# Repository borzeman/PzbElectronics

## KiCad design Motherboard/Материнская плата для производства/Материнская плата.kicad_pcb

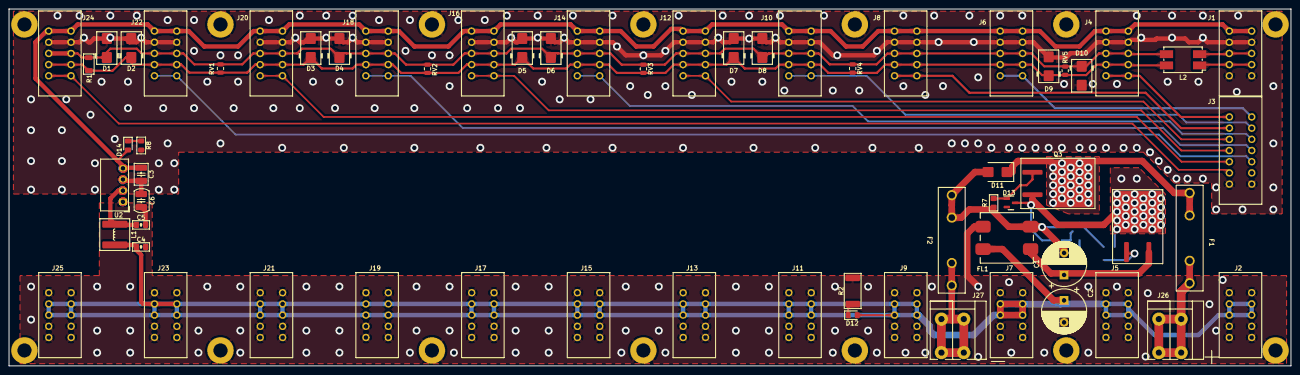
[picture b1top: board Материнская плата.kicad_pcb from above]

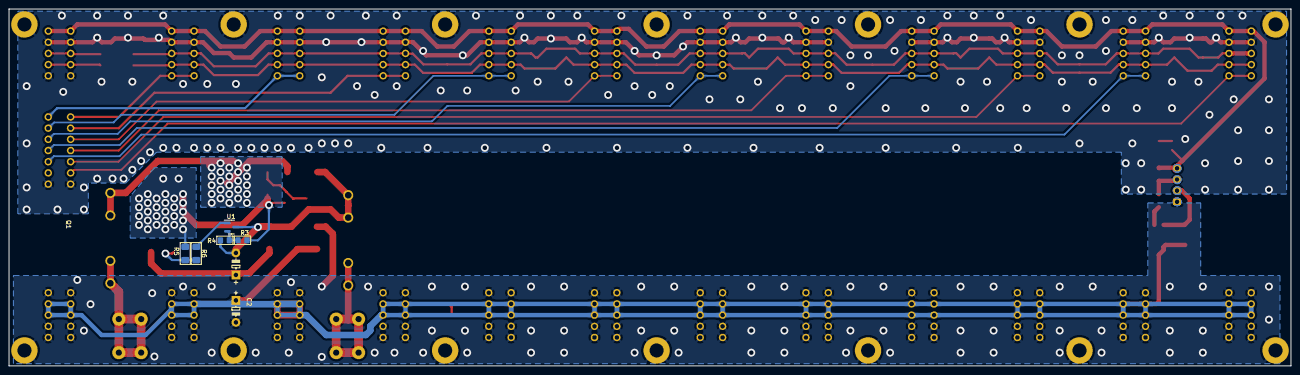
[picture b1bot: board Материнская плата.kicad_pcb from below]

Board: 2 copper layers, 291.0 x 81.0 mm, 83 parts (5 on the bottom side), 32 nets.

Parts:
C1, C2: 47uF 63V D10 H16; CP_Radial_D10.0mm_P5.00mm
C3: 10uF 50V 1210 GRM32ER71H106K; C_1210_3225Metric_Pad1.42x2.65mm_HandSolder
C4, C5: 4,7uF 50V 0805; C_0805_2012Metric_Pad1.18x1.45mm_HandSolder
C6: 270 pf X7R 1206 2000v 202R18W271KW4E; C_1210_3225Metric_Pad1.42x2.65mm
D1, D2, D3, D4, D5, D6, D7, D8, D9, D10: SMBJ5.0A (SMB); D_SMB
D11: SM6T30A (SMB); D_SMB
D12, D14: LED 0805 (FYLS-0805UBC); LED_0805_2012Metric_Pad1.15x1.40mm_HandSolder
D13: BZX84C10 (SOT-23); SOT-23
F1, F2: Fuse 10A ZH266 (2 клипсы); Fuseholder_100_series_5x20mm_D1,5
FL1: ACM70V-701-2PL-TL00; ACM12V
H1, H2, H3, H4, H5, H6, H7, H8, H9, H10, H11, H12, H13, H14: MountingHole_M3_3.2mm_Pad; MountingHole_3.2mm_Pad
J1, J2, J4, J5, J6, J7, J8, J9, J10, J11, J12, J13, J14, J15, J16, J17, J18, J19, J20, J21, J22, J23, J24, J25: SL-10 (L-KLS1-603C-10-S)
J3: SL-14 (L-KLS1-603C-14-S)
J26, J27: DG142V-5.08-02P-14
L1: 6,8uH 3,5A ETQP3M6R8KVP; L_Bourns-SRN6028
L2: B82790S0253N201; L_CommonMode_Delevan_4222
Q1, Q3: SUM110P06-08L-E3 (TO-263-2); TO-263-2
R1: 1206-120 Ом±5%-0,25 Вт; R_1206_3216Metric
R2: 2512-2,4 кОм±5%-1 Вт; R_2512_6332Metric_Pad1.52x3.35mm_HandSolder
R3, R7: 0805-10 кОм±5%-0,125 Вт; R_0805_2012Metric_Pad1.20x1.40mm_HandSolder
R4: 0805-1,5 кОм±5%-0,125 Вт; R_0805_2012Metric_Pad1.20x1.40mm_HandSolder
R5, R6: 1206-1 кОм±5%-0,25 Вт; R_1206_3216Metric_Pad1.42x1.75mm_HandSolder
R8: 0805-200 Ом±5%-0,125 Вт; R_0805_2012Metric_Pad1.15x1.40mm
RV1, RV2, RV3, RV4, RV5: JMV0805S5R6T661; R_0805_2012Metric
U1: TL431DBZ (sot-23); SOT-23
U2: AM1SS-2403SJZ; Converter_DCDC_Murata_CRE1xxxxxx3C_THT

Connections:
+24V: C2.1, C4.1, D12.2 (A), FL1.4, J2.2, J2.3, J2.8, J2.9, J5.2, J5.3, J5.8, J5.9, J7.2, J7.3, J7.8, J7.9, J9.2, J9.3, J9.8, J9.9, J11.2, J11.3, J11.8, J11.9, J13.2, J13.3, J13.8, J13.9, J15.2, J15.3, J15.8, J15.9, J17.2, J17.3, J17.8, J17.9, J19.2, J19.3, J19.8, J19.9, J21.2, J21.3, J21.8, J21.9, J23.2, J23.3, J23.8, J23.9, J25.2, J25.3, J25.8, J25.9, L1.1
/+3.3VRS485: C3.1, D14.2 (A), J1.1, J1.10, J4.1, J4.10, J6.1, J6.10, J8.1, J8.10, J10.1, J10.10, J12.1, J12.10, J14.1, J14.10, J16.1, J16.10, J18.1, J18.10, J20.1, J20.10, J22.1, J22.10, J24.1, J24.10, U2.4 (OUT+)
/A: D1.1 (K), D4.1 (K), D6.1 (K), D8.1 (K), D10.1 (K), J4.3, J4.8, J6.3, J6.8, J8.3, J8.8, J10.3, J10.8, J12.3, J12.8, J14.3, J14.8, J16.3, J16.8, J18.3, J18.8, J20.3, J20.8, J22.3, J22.8, J24.3, J24.8, L2.3, R1.1, RV1.1, RV2.1, RV3.1, RV4.1, RV5.1
/B: D2.1 (K), D3.1 (K), D5.1 (K), D7.1 (K), D9.1 (K), J4.4, J4.7, J6.4, J6.7, J8.4, J8.7, J10.4, J10.7, J12.4, J12.7, J14.4, J14.7, J16.4, J16.7, J18.4, J18.7, J20.4, J20.7, J22.4, J22.7, J24.4, J24.7, L2.4, R1.2, RV1.2, RV2.2, RV3.2, RV4.2, RV5.2
/RTS1: J3.1, J4.5, J4.6
/RTS2: J3.14, J6.5, J6.6
/RTS3: J3.2, J8.5, J8.6
/RTS4: J3.13, J10.5, J10.6
/RTS5: J3.3, J12.5, J12.6
/RTS6: J3.12, J14.5, J14.6
/RTS7: J3.4, J16.5, J16.6
/RTS8: J3.11, J18.5, J18.6
/RTS9: J3.5, J20.5, J20.6
/RTS10: J3.10, J22.5, J22.6
/RTS11: J3.6, J24.5, J24.6
GND1: C3.2, C6.2, D1.2 (A), D2.2 (A), D3.2 (A), D4.2 (A), D5.2 (A), D6.2 (A), D7.2 (A), D8.2 (A), D9.2 (A), D10.2 (A), H1.1, H2.1, H3.1, H4.1, H5.1, H6.1, H13.1, J1.2, J1.5, J1.6, J1.9, J3.7, J3.8, J4.2, J4.9, J6.2, J6.9, J8.2, J8.9, J10.2, J10.9, J12.2, J12.9, J14.2, J14.9, J16.2, J16.9, J18.2, J18.9, J20.2, J20.9, J22.2, J22.9, J24.2, J24.9, R8.2, U2.3 (OUT-)
GNDA: C2.2, C4.2, C5.2, C6.1, FL1.3, H7.1, H8.1, H9.1, H10.1, H11.1, H12.1, H14.1, J2.1, J2.4, J2.5, J2.6, J2.7, J2.10, J5.1, J5.4, J5.5, J5.6, J5.7, J5.10, J7.1, J7.4, J7.5, J7.6, J7.7, J7.10, J9.1, J9.4, J9.5, J9.6, J9.7, J9.10, J11.1, J11.4, J11.5, J11.6, J11.7, J11.10, J13.1, J13.4, J13.5, J13.6, J13.7, J13.10, J15.1, J15.4, J15.5, J15.6, J15.7, J15.10, J17.1, J17.4, J17.5, J17.6, J17.7, J17.10, J19.1, J19.4, J19.5, J19.6, J19.7, J19.10, J21.1, J21.4, J21.5, J21.6, J21.7, J21.10, J23.1, J23.4, J23.5, J23.6, J23.7, J23.10, J25.1, J25.4, J25.5, J25.6, J25.7, J25.10, R2.2, U2.1 (IN-)
unnamed: D11.1 (A1), F1.1, Q3.2 (D)
unnamed: C1.2, D11.2 (A2), F2.1, FL1.2, R4.2, R7.2, U1.3 (A)
unnamed: D12.1 (K), R2.1
unnamed: D13.1 (A), Q3.1 (G), R7.1
unnamed: D13.3 (K), Q1.2 (D), Q3.3 (S), R3.1, R5.1
unnamed: D14.1 (K), R8.1
unnamed: J1.3, J1.8, L2.2
unnamed: J1.4, J1.7, L2.1
unnamed: F1.2, J26.1, J26.2
unnamed: F2.2, J27.1, J27.2
unnamed: Q1.1 (G), R5.2, R6.1
unnamed: C1.1, FL1.1, Q1.3 (S)
unnamed: R6.2, U1.1 (K)
unnamed: R3.2, R4.1, U1.2 (REF)
unnamed: C5.1, L1.2, U2.2 (IN+)

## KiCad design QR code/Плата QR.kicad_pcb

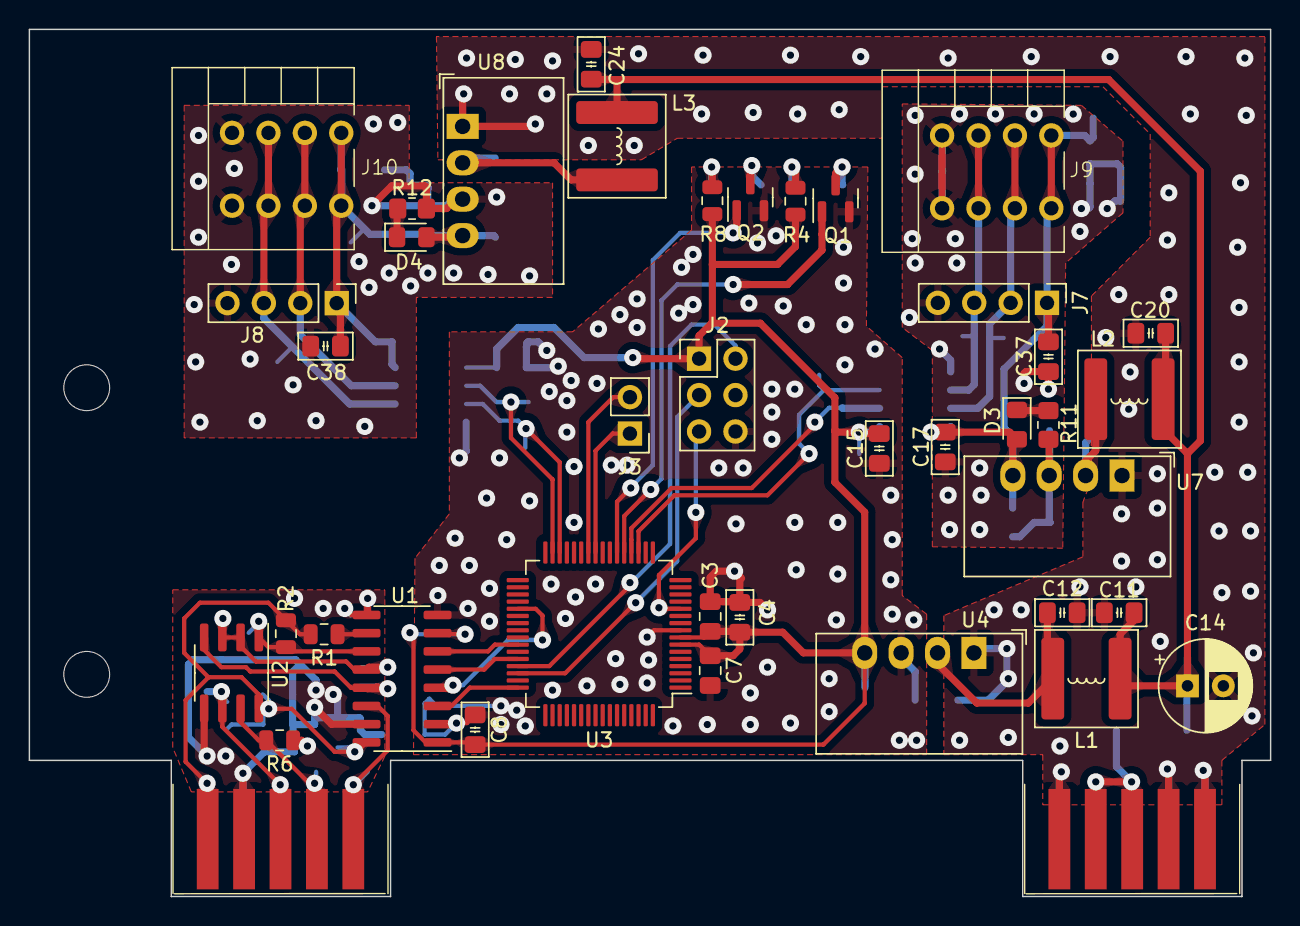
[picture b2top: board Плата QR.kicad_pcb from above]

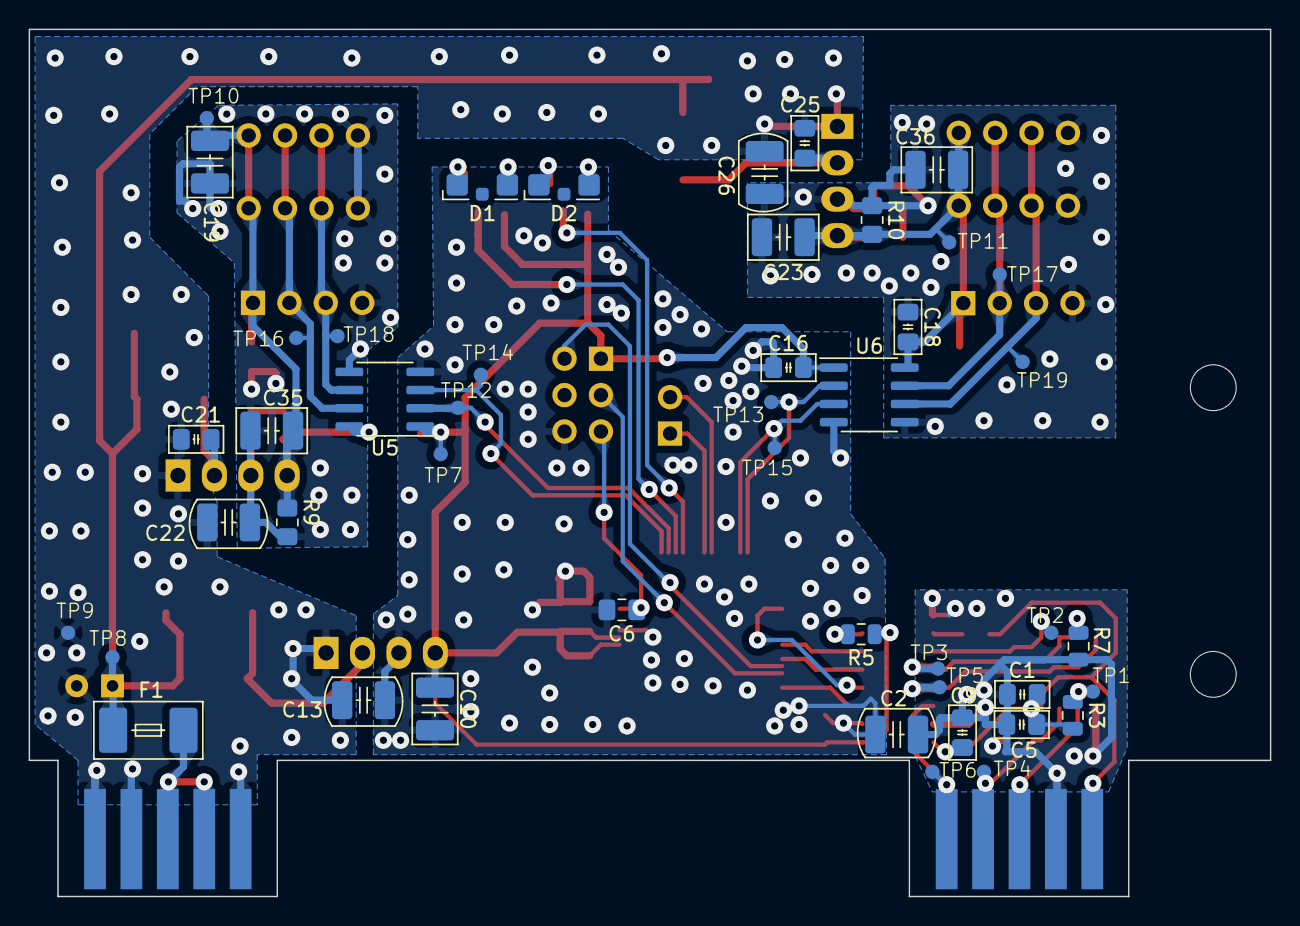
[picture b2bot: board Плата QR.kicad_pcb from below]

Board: 2 copper layers, 86.6 x 60.5 mm, 89 parts (46 on the bottom side), 47 nets.

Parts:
C1: 1uF 100V 0805; C_0805_2012Metric_Pad1.18x1.45mm_HandSolder
C2, C13, C22, C26: 270 pf X7R 1206 2000v 202R18W271KW4E; C_1210_3225Metric_Pad1.42x2.65mm
C3, C6, C7: 0,1uF 50V 0805; C_0805_2012Metric_Pad1.18x1.45mm_HandSolder
C4, C11, C12, C20, C21, C24, C25: 4,7uF 50V 0805; C_0805_2012Metric_Pad1.18x1.45mm_HandSolder
C5, C8, C9, C15, C16, C17, C18, C37, C38: 0,1uF 100V 0805; C_0805_2012Metric_Pad1.18x1.45mm_HandSolder
C10, C19, C23, C35, C36: 10uF 50V 1210 GRM32ER71H106K; C_1210_3225Metric_Pad1.42x2.65mm_HandSolder
C14: 47uF 63V D10,5; CP_Radial_D6.3mm_P2.50mm
D1, D2: KPA-3010CGCK; LED_Kingbright_KPA-3010_3x2x1mm
D3, D4: LED 0805 (LTST-C170KGKT); LED_0805_2012Metric_Pad1.15x1.40mm_HandSolder
F1: 0452.500MRL; Fuse_Littelfuse-NANO2-451_453
H1, H2: MountingHole; MountingHole_3.2mm_M3
J2: Prog (PinHeader_2x03_P2.54mm); PinHeader_2x03_P2.54mm_Vertical
J3: Debbag GPIO (PinHeader_01x02_P2.54mm); PinHeader_1x02_P2.54mm_Vertical
J7, J8: Usart_debbag; PinHeader_1x04_P2.54mm_Vertical
J9, J10: DG141R-04
L1, L2, L3: 6,8uH 3,5A ETQP3M6R8KVP; L_Bourns-SRN6028
Q1, Q2: DTC114ECA (SOT-23); SOT-23
R1, R5: 0805-4,7 кОм±5%-0,125 Вт; R_0805_2012Metric
R2, R7: 0805-10 кОм±5%-0,125 Вт; R_0805_2012Metric
R3, R6: 0805-560 Ом±5%-0,125 Вт; R_0805_2012Metric
R4, R8: 0805-150 Ом±5%-0,125 Вт; R_0805_2012Metric
R9, R10: 0805 161; R_0805_2012Metric_Pad1.20x1.40mm_HandSolder
R11, R12: 0805 750; R_0805_2012Metric_Pad1.20x1.40mm_HandSolder
RS1, RS2: SL-10 (L-KLS1-603C-10-S); Edge_Conn_KLS1-603-10
TP1, TP2, TP3, TP4, TP5, TP6, TP7, TP8, TP9, TP10, TP11, TP12, TP13, TP14, TP15, TP16, TP17, TP18, TP19: TestPoint; TestPoint_D1
U1: pia141M30 (SOIC-16); SOIC-16_3.9x9.9mm_P1.27mm
U2: ADM3485EARZ-REEL (SOIC-8); SOIC-8_3.9x4.9mm_P1.27mm
U3: STM32G070RBTx (LQFP-64); LQFP-64_10x10mm_P0.5mm
U4, U7, U8: AM1SS-2403SJZ; Converter_DCDC_Murata_MEE3SxxxxSC_THT
U5, U6: Pai122E30; SOIC-8_3.9x4.9mm_P1.27mm

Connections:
+3V3: C3.1, C4.1, C7.1, C8.2, C10.1, C15.2, C16.2, J2.1, R4.2, R5.1, R8.1, TP7.1, U1.1 (VDD1), U3.7 (VREF+), U3.8 (VDD), U4.4 (OUT+), U5.1 (VDD1), U6.1 (VDD1)
+24V: C11.1, C14.1, C20.1, C24.1, F1.2, L1.1, L2.1, L3.1, TP8.1
/+3.3VRS485: C1.2, C5.2, C9.2, R1.2, R2.2, R3.2, RS1.1, RS1.10, U1.16 (VDD2), U2.8 (VCC)
/DE_USART_1: U1.5 (VIC), U3.44 (PA12/PA10)
/GND_1: C17.1, C19.2, C22.2, C35.2, C37.1, J7.4, J9.4, R9.1, R11.1, U5.5 (GND2), U7.3 (OUT-)
/GND_2: C18.1, C23.2, C26.2, C36.2, C38.1, J8.4, J10.4, R10.1, R12.1, U6.5 (GND2), U8.3 (OUT-)
/GPIO1: J3.1, U3.25 (PC4)
/GPIO2: J3.2, U3.26 (PC5)
/NRST: C6.1, J2.5, U3.12 (NRST)
/RTS: RS1.5, RS1.6, TP6.1, U1.14 (VOA)
/RTS_cont: U1.3 (VIA), U3.48 (PC8)
/RX_1: J7.2, J9.2, TP16.1, U5.7 (VIA)
/RX_2: J8.2, J10.2, TP17.1, U6.7 (VIA)
/RX_USART_1: U1.6 (VOD), U3.42 (PA10/NC)
/RX_USART_OUT1: TP12.1, U3.20 (PA3), U5.2 (VOA)
/RX_USART_OUT2: TP13.1, U3.31 (PB11), U6.2 (VOA)
/SWCLK: J2.3, U3.46 (PA14)
/SWDIO: J2.2, U3.45 (PA13)
/TX_1: J7.3, J9.3, TP18.1, U5.6 (VOB)
/TX_2: J8.3, J10.3, TP19.1, U6.6 (VOB)
/TX_USART_1: U1.4 (VIB), U3.37 (PA9/NC)
/TX_USART_OUT1: TP14.1, U3.19 (PA2), U5.3 (VIB)
/TX_USART_OUT2: TP15.1, U3.30 (PB10), U6.3 (VIB)
/Vcc_1: C17.2, C19.1, C35.1, C37.2, D3.2 (A), J7.1, J9.1, R9.2, TP10.1, U5.8 (VDD2), U7.4 (OUT+)
/Vcc_2: C18.2, C23.1, C36.1, C38.2, D4.2 (A), J8.1, J10.1, R10.2, TP11.1, U6.8 (VDD2), U8.4 (OUT+)
GND1: C1.1, C2.1, C5.1, C9.1, R6.1, R7.1, RS1.2, RS1.9, U1.9 (GND2), U1.15 (GND2), U2.5 (GND)
GNDA: C11.2, C12.2, C13.1, C14.2, C20.2, C21.2, C22.1, C24.2, C25.2, C26.1, RS2.1, RS2.4, RS2.5, RS2.6, RS2.7, RS2.10, TP9.1, U4.1 (IN-), U7.1 (IN-), U8.1 (IN-)
GNDD: C2.2, C3.2, C4.2, C6.2, C7.2, C8.1, C10.2, C13.2, C15.1, C16.1, J2.6, Q1.2 (E), Q2.2 (E), U1.2 (GND1), U1.8 (GND1), U3.9 (VSS), U4.3 (OUT-), U5.4 (GND1), U6.4 (GND1)
unnamed: D1.2 (A), R4.1
unnamed: D1.1 (K), Q1.3 (C)
unnamed: D2.2 (A), R8.2
unnamed: D2.1 (K), Q2.3 (C)
unnamed: D3.1 (K), R11.2
unnamed: D4.1 (K), R12.2
unnamed: Q1.1 (B), U3.21 (PA4)
unnamed: Q2.1 (B), U3.22 (PA5)
unnamed: R3.1, RS1.3, RS1.8, TP1.1, U2.6 (A)
unnamed: R6.2, RS1.4, RS1.7, TP4.1, U2.7 (B)
unnamed: F1.1, RS2.2, RS2.3, RS2.8, RS2.9
unnamed: R5.2, U1.7 (VE1)
unnamed: R1.1, U1.10 (VE2)
unnamed: R2.1, TP2.1, U1.11 (VID), U2.1 (RO)
unnamed: TP5.1, U1.13 (VOB), U2.4 (DI)
unnamed: R7.2, TP3.1, U1.12 (VOC), U2.2 (~RE), U2.3 (DE)
unnamed: C12.1, L1.2, U4.2 (IN+)
unnamed: C21.1, L2.2, U7.2 (IN+)
unnamed: C25.1, L3.2, U8.2 (IN+)

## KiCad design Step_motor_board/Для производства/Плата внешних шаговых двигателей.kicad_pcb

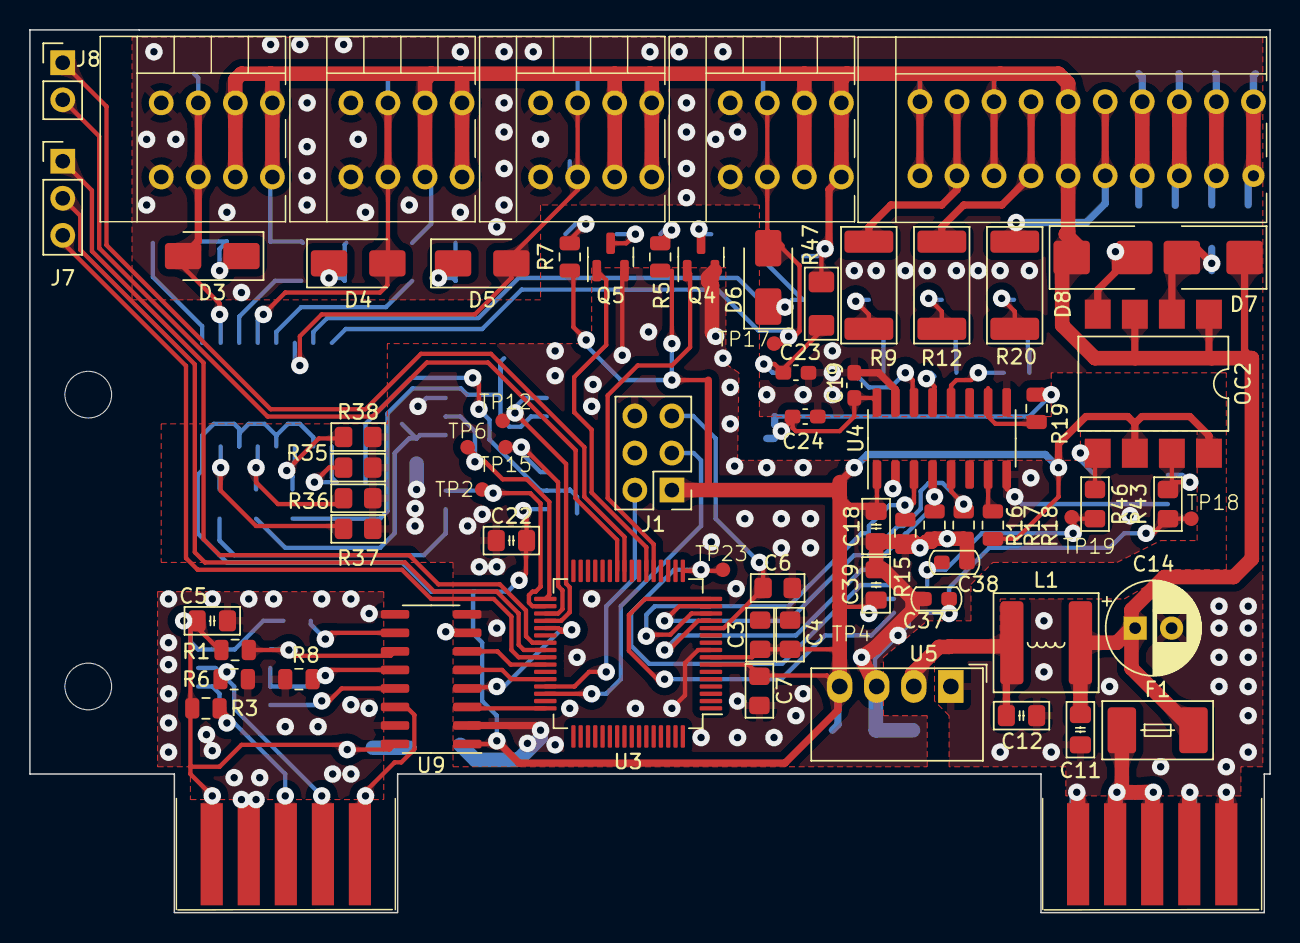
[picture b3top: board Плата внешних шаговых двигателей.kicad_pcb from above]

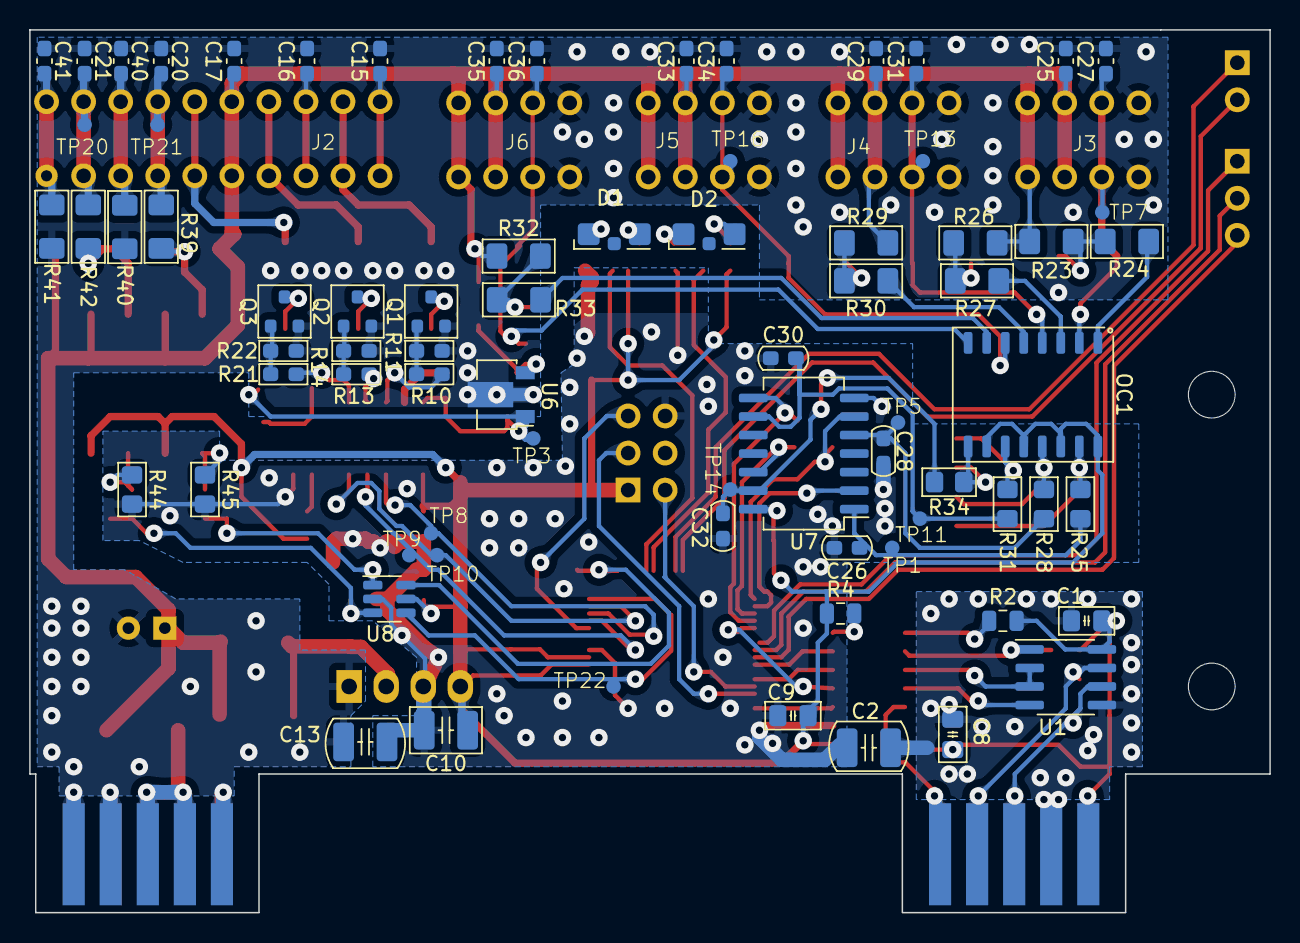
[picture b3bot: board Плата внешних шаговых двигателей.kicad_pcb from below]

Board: 2 copper layers, 85.0 x 60.5 mm, 148 parts (75 on the bottom side), 89 nets.

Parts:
C1: 1uF 100V 0805; C_0805_2012Metric_Pad1.18x1.45mm_HandSolder
C2, C13: 270 pf X7R 1206 2000v 202R18W271KW4E; C_1210_3225Metric_Pad1.42x2.65mm
C3, C6, C7: 0,1uF 50V 0805; R_0805_2012Metric_Pad1.20x1.40mm_HandSolder
C4: 4,7uF 50V 0805; R_0805_2012Metric_Pad1.20x1.40mm_HandSolder
C5, C8, C9, C18, C22, C39: 0,1uF 100V 0805; C_0805_2012Metric_Pad1.18x1.45mm_HandSolder
C10: 10uF 50V 1210 GRM32ER71H106K; C_1210_3225Metric_Pad1.42x2.65mm_HandSolder
C11, C12: 4,7uF 50V 0805; C_0805_2012Metric_Pad1.18x1.45mm_HandSolder
C14: 47uF 63V D10,5; CP_Radial_D6.3mm_P2.50mm
C15, C16, C17, C19, C20, C21, C24, C25, C27, C29, C31, C33, C34, C35, C36, C40, C41: 0,1uF 50V 0603; C_0603_1608Metric_Pad1.08x0.95mm_HandSolder
C23: 0,33uF 50V 0603; C_0603_1608Metric_Pad1.08x0.95mm_HandSolder
C26, C28, C30, C32, C37, C38: 0,01uF 50V 0603; C_0603_1608Metric_Pad1.08x0.95mm
D1, D2: KPA-3010CGCK; LED_Kingbright_KPA-3010_3x2x1mm
D3, D4, D5, D6: SMAJ12A (SMA); D_SMA
D7, D8: SMBJ3.3A (SMB); D_SMB
F1: 0452.500MRL; Fuse_Littelfuse-NANO2-451_453
H1, H2: MountingHole; MountingHole_3.2mm_M3
J1: Prog (PinHeader_2x03_P2.54mm); PinHeader_2x03_P2.54mm_Vertical
J2: Driver (DG141R-10); DG141R-10
J3: DI2 (DG141R-04); DG141R-04
J4: DI1 (DG141R-04); DG141R-04
J5: DI3 (DG141R-04); DG141R-04
J6: DI4 (DG141R-04); DG141R-04
J7: DebugUSART (PinHeader_01x03_P2.54mm); PinHeader_1x03_P2.54mm_Vertical
J8: Debug GPIO (PinHeader_01x02_P2.54mm); PinHeader_1x02_P2.54mm_Vertical
L1: 6,8uH 3,5A ETQP3M6R8KVP; L_Bourns-SRN6028
OC1: IS281- 4 (SOIC-16W); SOIC-16W_5.3x10.2mm_P1.27mm
OC2: LTV-827S (SMDIP-8); SMDIP-8_W9.53mm
Q1, Q2, Q3: 2SC2712 (SOT-23); SOT-23
Q4, Q5: DTC114ECA (SOT-23); SOT-23
R1, R8, R15, R16, R17: 0805-10 кОм±5%-0,125 Вт; R_0805_2012Metric
R2, R4, R18, R19: 0805-4,7 кОм±5%-0,125 Вт; R_0805_2012Metric
R3, R6: 0805-560 Ом±5%-0,125 Вт; R_0805_2012Metric
R5, R7: 0805-150 Ом±5%-0,125 Вт; R_0805_2012Metric
R9, R12, R20: 2512-2,4 кОм±5%-1 Вт; R_2512_6332Metric_Pad1.52x3.35mm_HandSolder
R10, R11, R13, R14, R21, R22: 0603-10 кОм±5%-0,062 Вт; R_0603_1608Metric_Pad1.05x0.95mm_HandSolder
R23, R24, R26, R27, R29, R30, R32, R33, R39, R40, R41, R42: 1206-1 кОм±5%-0,25 Вт; R_1206_3216Metric_Pad1.42x1.75mm_HandSolder
R25, R28, R31, R34, R43, R46: 0805-1 кОм±5%-0,125 Вт; R_0805_2012Metric_Pad1.20x1.40mm_HandSolder
R35, R36, R37, R38, R44, R45: 0805-10 кОм±5%-0,125 Вт; R_0805_2012Metric_Pad1.20x1.40mm_HandSolder
R47: 1206-620 Ом±5%-0,25 Вт; R_1206_3216Metric_Pad1.42x1.75mm_HandSolder
RS1, RS2: SL-10 (L-KLS1-603C-10-S); Edge_Conn_KLS1-603-10
TP1, TP2, TP3, TP4, TP5, TP6, TP7, TP8, TP9, TP10, TP11, TP12, TP13, TP14, TP15, TP16, TP17, TP18, TP19, TP20, TP21, TP22, TP23: TestPoint; TestPoint_D1
U1: ADM3485EARZ-REEL (SOIC-8); SOIC-8_3.9x4.9mm_P1.27mm
U3: STM32G070RBTx (LQFP-64); LQFP-64_10x10mm_P0.5mm
U4, U9: pia141M30 (SOIC-16); SOIC-16_3.9x9.9mm_P1.27mm
U5: AM1SS-2403SJZ; Converter_DCDC_Murata_MEE1SxxxxSC_THT
U6: L78L05 (SOT89-3); SOT-89-3
U7: HEF40106BT (SO-14); SO-14_5.3x10.2mm_P1.27mm
U8: 74LVC2G14 (SOT-23-6); SOT-23-6

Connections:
+3V3: C3.1, C4.1, C7.1, C9.2, C10.1, C18.2, C22.2, C39.2, J1.1, OC1.10, OC1.12, OC1.14, OC1.16, OC2.6, OC2.8, R4.1, R5.2, R7.1, R18.1, TP4.1, U3.7 (VREF+), U3.8 (VDD), U4.1 (VDD1), U5.4 (OUT+), U7.14 (VDD), U8.5 (VCC), U9.1 (VDD1)
+5V: C19.1, C24.1, R19.1, TP3.1, U4.16 (VDD2), U6.1 (OUT)
+24V: C11.1, C14.1, C15.1, C16.1, C17.1, C25.1, C29.1, C33.1, C35.1, D7.1 (K), D8.1 (K), F1.2, J2.6, J2.8, J2.10, J3.1, J3.2, J4.1, J4.2, J5.1, J5.2, J6.1, J6.2, L1.1, OC2.1, OC2.3, R23.1, R26.1, R29.1, R32.1, R47.2
/+3.3VRS485: C1.2, C5.2, C8.2, R1.2, R2.2, R3.2, RS1.1, RS1.10, U1.8 (VCC), U9.16 (VDD2)
/ALARM: TP22.1, U3.16 (PC3), U8.4
/DE_USART_1: U3.44 (PA12/PA10), U9.5 (VIC)
/DI1: TP6.1, U3.33 (PB13), U7.6
/DI2: TP2.1, U3.34 (PB14), U7.2
/DI3: TP12.1, U3.36 (PA8), U7.8
/DI4: TP15.1, U3.35 (PB15), U7.12
/DIR: R16.2, TP9.1, U3.13 (PC0), U4.4 (VIB)
/EN: R15.2, TP8.1, U3.14 (PC1), U4.3 (VIA)
/GPIO1: J8.1, U3.25 (PC4)
/GPIO2: J8.2, U3.26 (PC5)
/IN_POSITION: TP23.1, U3.17 (PA0), U8.6
/NRST: C6.1, J1.5, U3.12 (NRST)
/RTS: RS1.5, RS1.6, U9.14 (VOA)
/RTS_cont: U3.48 (PC8), U9.3 (VIA)
/RX_USART_1: U3.42 (PA10/NC), U9.6 (VOD)
/STEP: R17.2, TP10.1, U3.15 (PC2), U4.5 (VIC)
/SWCLK: J1.3, U3.46 (PA14)
/SWDIO: J1.2, U3.45 (PA13)
/Stepper_Motor_Control/ALARM_out+: C21.1, J2.2, R42.2, TP20.1
/Stepper_Motor_Control/DIR_out-: J2.7, R12.1
/Stepper_Motor_Control/EN_out-: J2.9, R9.1
/Stepper_Motor_Control/IN_POSITION_out+: C20.1, J2.4, R39.2, TP21.1
/Stepper_Motor_Control/STEP_out-: J2.5, R20.1
/TX_USART_1: U3.37 (PA9/NC), U9.4 (VIB)
/UART_DE: J7.1, U3.39 (PC7)
/UART_RX: J7.3, U3.41 (PD9)
/UART_TX: J7.2, U3.40 (PD8)
GND1: C1.1, C2.1, C5.1, C8.1, R6.1, R8.1, RS1.2, RS1.9, U1.5 (GND), U9.9 (GND2), U9.15 (GND2)
GNDA: C11.2, C12.2, C13.1, C14.2, C15.2, C16.2, C17.2, C19.2, C20.2, C21.2, C23.2, C24.2, C25.2, C27.2, C29.2, C31.2, C33.2, C34.2, C35.2, C36.2, C40.2, C41.2, J3.4, J4.4, J5.4, J6.4, Q1.2 (E), Q2.2 (E), Q3.2 (E), R11.1, R14.1, R22.1, R40.1, R41.2, RS2.1, RS2.4, RS2.5, RS2.6, RS2.7, RS2.10, U4.9 (GND2), U4.15 (GND2), U5.1 (IN-), U6.2 (GND)
GNDD: C2.2, C3.2, C4.2, C6.2, C7.2, C9.1, C10.2, C13.2, C18.1, C22.1, C26.2, C28.2, C30.2, C32.2, C37.2, C38.2, C39.1, J1.6, Q4.2 (E), Q5.2 (E), R15.1, R16.1, R17.1, R35.2, R36.2, R37.2, R38.2, R44.2, R45.2, U3.9 (VSS), U4.2 (GND1), U4.8 (GND1), U5.3 (OUT-), U7.7 (VSS), U8.2 (GND), U9.2 (GND1), U9.8 (GND1)
unnamed: C26.1, R25.2, TP1.1, U7.1
unnamed: C28.1, R28.2, TP5.1, U7.5
unnamed: C30.1, R31.2, TP11.1, U7.9
unnamed: C32.1, R34.2, TP14.1, U7.13
unnamed: C37.1, R43.2, TP18.1, U8.3
unnamed: C38.1, R46.2, TP19.1, U8.1
unnamed: D1.2 (A), R5.1
unnamed: D1.1 (K), Q4.3 (C)
unnamed: D2.2 (A), R7.2
unnamed: D2.1 (K), Q5.3 (C)
unnamed: D3.1 (A1), R23.2, R24.1
unnamed: C27.1, D3.2 (A2), J3.3, OC1.2, TP7.1
unnamed: D4.1 (A1), R26.2, R27.1
unnamed: C31.1, D4.2 (A2), J4.3, OC1.4, TP13.1
unnamed: D5.1 (A1), R29.2, R30.1
unnamed: C34.1, D5.2 (A2), J5.3, OC1.6, TP16.1
unnamed: D6.1 (A1), R32.2, R33.1
unnamed: C36.1, D6.2 (A2), J6.3, OC1.8, TP17.1
unnamed: D7.2 (A), OC2.2, R42.1
unnamed: D8.2 (A), OC2.4, R39.1
unnamed: C41.1, J2.1, R41.1
unnamed: C40.1, J2.3, R40.2
unnamed: OC1.1, R24.2
unnamed: OC1.3, R27.2
unnamed: OC1.5, R30.2
unnamed: OC1.7, R33.2
unnamed: OC1.9, R34.1, R35.1
unnamed: OC1.11, R31.1, R38.1
unnamed: OC1.13, R28.1, R36.1
unnamed: OC1.15, R25.1, R37.1
unnamed: OC2.5, R45.1, R46.1
unnamed: OC2.7, R43.1, R44.1
unnamed: Q1.1 (B), R10.1, R11.2
unnamed: Q1.3 (C), R9.2
unnamed: Q2.1 (B), R13.1, R14.2
unnamed: Q2.3 (C), R12.2
unnamed: Q3.1 (B), R21.1, R22.2
unnamed: Q3.3 (C), R20.2
unnamed: Q4.1 (B), U3.21 (PA4)
unnamed: Q5.1 (B), U3.22 (PA5)
unnamed: R3.1, RS1.3, RS1.8, U1.6 (A)
unnamed: R6.2, RS1.4, RS1.7, U1.7 (B)
unnamed: F1.1, RS2.2, RS2.3, RS2.8, RS2.9
unnamed: R8.2, U1.2 (~RE), U1.3 (DE), U9.12 (VOC)
unnamed: U1.4 (DI), U9.13 (VOB)
unnamed: R1.1, U1.1 (RO), U9.11 (VID)
unnamed: R18.2, U4.7 (VE1)
unnamed: R19.2, U4.10 (VE2)
unnamed: R10.2, U4.14 (VOA)
unnamed: R13.2, U4.13 (VOB)
unnamed: R21.2, U4.12 (VOC)
unnamed: C12.1, L1.2, U5.2 (IN+)
unnamed: C23.1, R47.1, U6.3 (IN)
unnamed: R4.2, U9.7 (VE1)
unnamed: R2.1, U9.10 (VE2)

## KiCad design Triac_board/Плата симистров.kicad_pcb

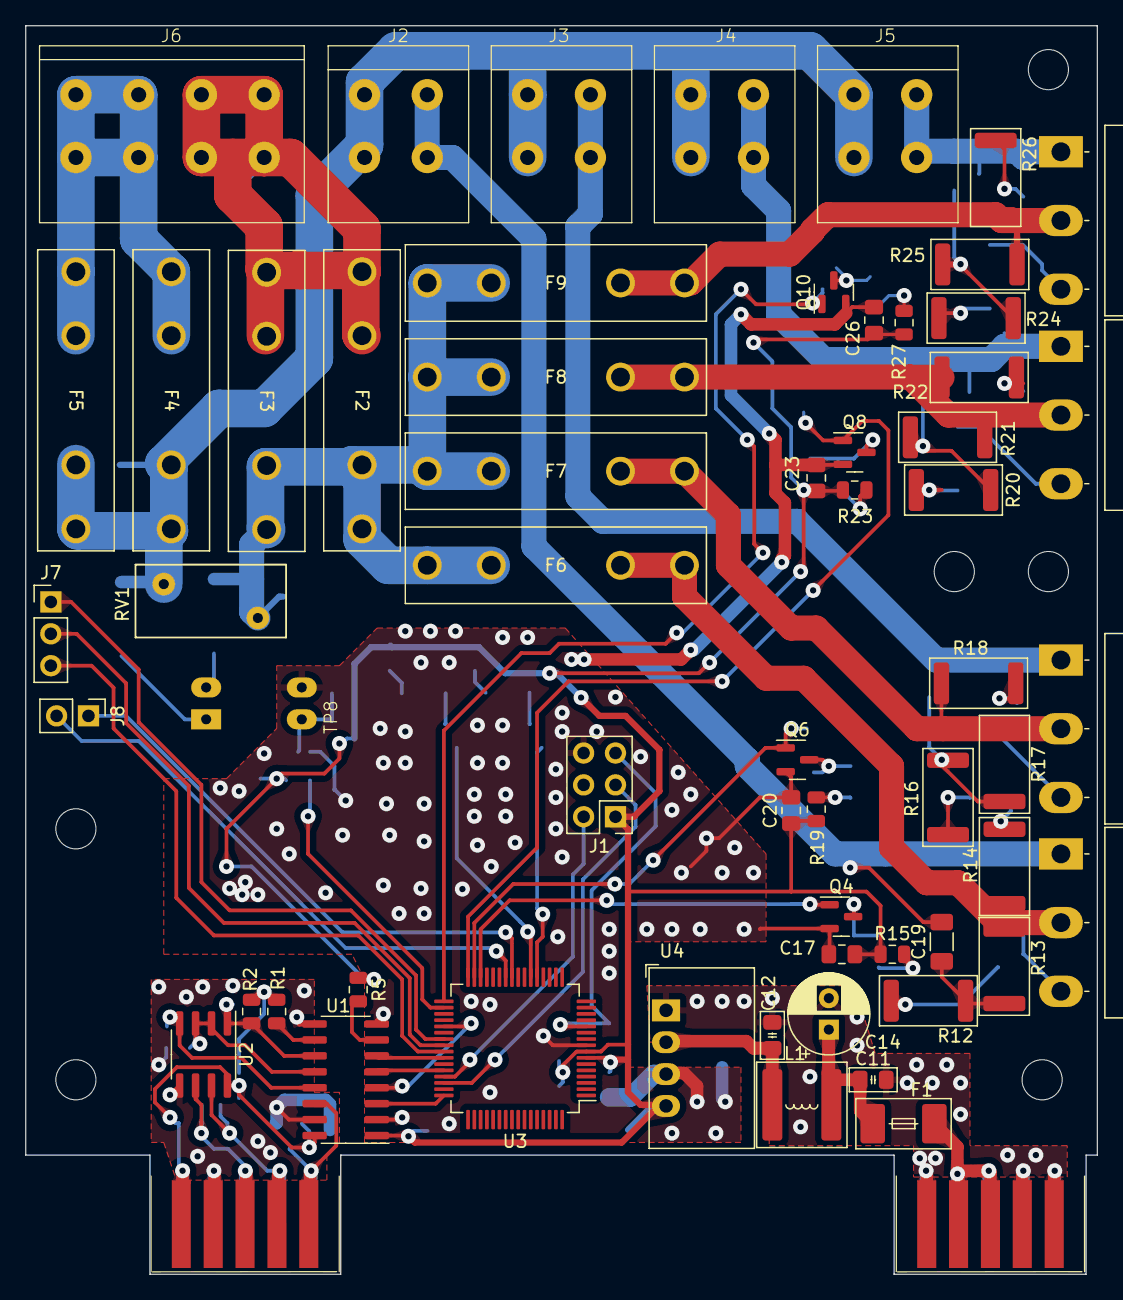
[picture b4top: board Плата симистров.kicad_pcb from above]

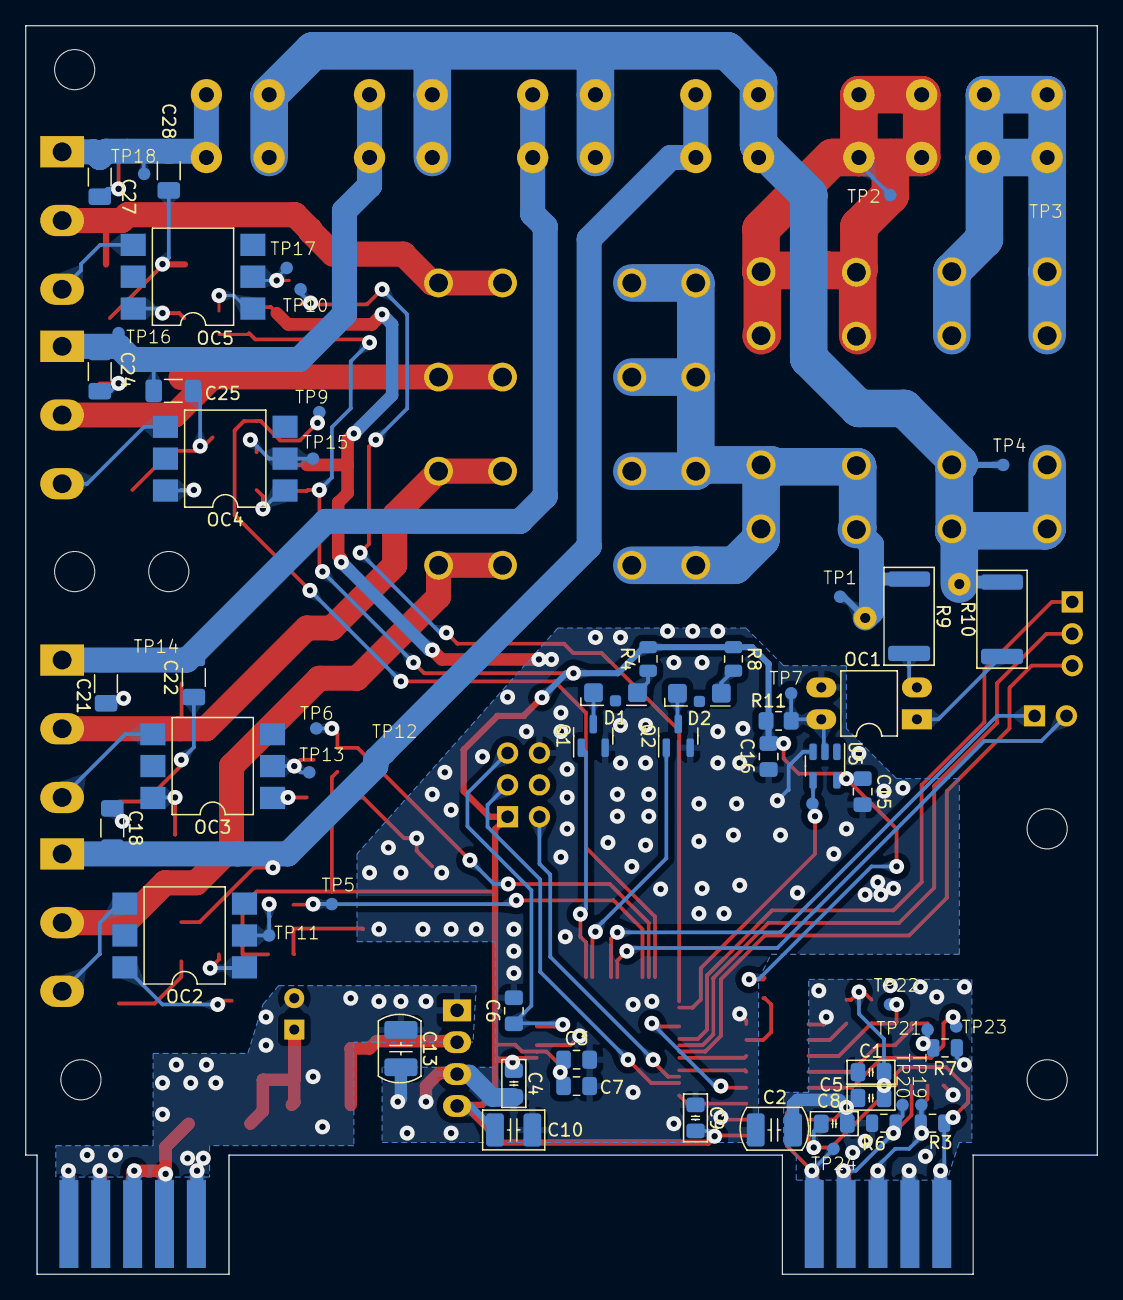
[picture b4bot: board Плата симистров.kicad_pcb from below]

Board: 2 copper layers, 85.4 x 99.5 mm, 128 parts (62 on the bottom side), 78 nets.

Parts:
C1: 1uF 100V 0805; C_0805_2012Metric_Pad1.18x1.45mm_HandSolder
C2, C13: 270 pf X7R 1206 2000v 202R18W271KW4E; C_1210_3225Metric_Pad1.42x2.65mm
C3, C6, C7, C15, C16, C17, C20, C23, C26: 0,1uF 50V 0805; C_0805_2012Metric_Pad1.18x1.45mm_HandSolder
C4, C11, C12: 4,7uF 50V 0805; C_0805_2012Metric_Pad1.18x1.45mm_HandSolder
C5, C8, C9: 0,1uF 100V 0805; C_0805_2012Metric_Pad1.18x1.45mm_HandSolder
C10: 10uF 50V 1210 GRM32ER71H106K; C_1210_3225Metric_Pad1.42x2.65mm_HandSolder
C14: 47uF 63V D10,5; CP_Radial_D6.3mm_P2.50mm
C18, C19, C21, C22, C24, C25, C27, C28: 0,01uF 600V 1206 (GRM31BR72J103KW01L); C_1206_3216Metric_Pad1.33x1.80mm_HandSolder
D1, D2: KPA-3010CGCK; LED_Kingbright_KPA-3010_3x2x1mm
F1: 0452.500MRL; Fuse_Littelfuse-NANO2-451_453
F2, F3, F4, F5, F6, F7, F8, F9: Fuse 10A ZH266 (2 клипсы); Fuseholder_100_series_5x20mm_D1,5
H1, H1#2, H1#3, H1#4, H1#5, H2: MountingHole; MountingHole_3.2mm_M3
J1: Prog (PinHeader_2x03_P2.54mm); PinHeader_2x03_P2.54mm_Vertical
J2, J3, J4, J5: DG245-5.0-02P
J6: DG245-5.0-04P
J7: DebbagUSART (PinHeader_01x03_P2.54mm); PinHeader_1x03_P2.54mm_Vertical
J8: Debbag GPIO (PinHeader_01x02_P2.54mm); PinHeader_1x02_P2.54mm_Vertical
L1: 6,8uH 3,5A ETQP3M6R8KVP; L_Bourns-SRN6028
OC1: FOD814; DIP-4_W7.62mm_LongPads
OC2, OC3, OC4, OC5: MOC3023SM (SMDIP-6); SMDIP-6_W9.53mm
Q1, Q2, Q4, Q6, Q8, Q10: DTC114ECA (SOT-23); SOT-23
Q3, Q5, Q7, Q9: BTA41-600B (TO-218); TO-218-3_Horizontal_TabDown
R1, R5: 0805-4,7 кОм±5%-0,125 Вт; R_0805_2012Metric
R2, R7: 0805-10 кОм±5%-0,125 Вт; R_0805_2012Metric
R3, R6: 0805-560 Ом±5%-0,125 Вт; R_0805_2012Metric
R4, R8: 0805-150 Ом±5%-0,125 Вт; R_0805_2012Metric
R9, R10: 2512-51 кОм±5%-1 Вт; R_2512_6332Metric
R11: 0805-1 кОм±5%-0,125 Вт; R_0805_2012Metric_Pad1.20x1.40mm_HandSolder
R12, R16, R20, R24: 2512-180 Ом±5%-1 Вт; R_2512_6332Metric
R13, R17, R21, R25: 2512-1 кОм±5%-1 Вт; R_2512_6332Metric
R14, R18, R22, R26: 2512-51 Ом±5%-1 Вт; R_2512_6332Metric
R15, R19, R23, R27: 0805-200 Ом±5%-0,125 Вт; R_0805_2012Metric
RS1, RS2: SL-10 (L-KLS1-603C-10-S); Edge_Conn_KLS1-603-10
RV1: V10E250P; RV_Disc_D12mm_W5.8mm_P7.5mm
TP1, TP2, TP3, TP4, TP5, TP6, TP7, TP8, TP9, TP10, TP11, TP12, TP13, TP14, TP15, TP16, TP17, TP18, TP19, TP20, TP21, TP22, TP23, TP24: TestPoint; TestPoint_D1
U1: pia141M30 (SOIC-16); SOIC-16_3.9x9.9mm_P1.27mm
U2: ADM3485EARZ-REEL (SOIC-8); SOIC-8_3.9x4.9mm_P1.27mm
U3: STM32G070RBTx (LQFP-64); LQFP-64_10x10mm_P0.5mm
U4: AM1SS-2403SJZ; Converter_DCDC_Murata_MEE3SxxxxSC_THT
U5: 74AHCT1G14GW,125; SOT-23-5

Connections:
+3V3: C3.1, C4.1, C7.1, C9.2, C10.1, C15.1, C16.1, C17.1, C20.1, C23.1, C26.1, J1.1, R4.2, R5.1, R8.1, R11.2, R15.1, R19.1, R23.1, R27.1, U1.1 (VDD1), U3.7 (VREF+), U3.8 (VDD), U4.4 (OUT+), U5.5 (VCC)
+24V: C11.1, C14.1, F1.2, L1.1
/+3.3VRS485: C1.2, C5.2, C8.2, R1.2, R2.2, R3.2, RS1.1, RS1.10, U1.16 (VDD2), U2.8 (VCC)
/DE_USART_1: U1.5 (VIC), U3.44 (PA12/PA10)
/GPIO1: J8.1, U3.25 (PC4)
/GPIO2: J8.2, U3.26 (PC5)
/NRST: C6.1, J1.5, U3.12 (NRST)
/RTS: RS1.5, RS1.6, TP24.1, U1.14 (VOA)
/RTS_cont: U1.3 (VIA), U3.48 (PC8)
/RX_USART_1: U1.6 (VOD), U3.42 (PA10/NC)
/SIM_1: Q4.1 (B), TP5.1, U3.30 (PB10)
/SIM_2: Q6.1 (B), TP6.1, U3.31 (PB11)
/SIM_3: Q8.1 (B), TP9.1, U3.32 (PB12)
/SIM_4: Q10.1 (B), TP10.1, U3.33 (PB13)
/SWCLK: J1.3, U3.46 (PA14)
/SWDIO: J1.2, U3.45 (PA13)
/Simisters/ACIN_1: F2.2, F3.2, F6.1, F7.1, F8.1, F9.1, R9.1, RV1.1, TP1.1
/Simisters/ACIN_2: F4.2, F5.2, J2.1, J3.1, J4.1, J5.1, R10.2, RV1.2, TP4.1
/Simisters/Simister1/AC_IN: F6.2, Q3.2 (A2), R13.1, R14.2
/Simisters/Simister1/AC_OUT: C18.2, C19.2, J2.2, Q3.1 (A1), TP12.1
/Simisters/Simister2/AC_IN: F7.2, Q5.2 (A2), R17.1, R18.2
/Simisters/Simister2/AC_OUT: C21.2, C22.2, J3.2, Q5.1 (A1), TP14.1
/Simisters/Simister3/AC_IN: F8.2, Q7.2 (A2), R21.1, R22.2
/Simisters/Simister3/AC_OUT: C24.2, C25.2, J4.2, Q7.1 (A1), TP16.1
/Simisters/Simister4/AC_IN: F9.2, Q9.2 (A2), R25.1, R26.2
/Simisters/Simister4/AC_OUT: C27.2, C28.2, J5.2, Q9.1 (A1), TP18.1
/TX_USART_1: U1.4 (VIB), U3.37 (PA9/NC)
/UART_DE: J7.1, U3.39 (PC7)
/UART_RX: J7.3, U3.41 (PD9)
/UART_TX: J7.2, U3.40 (PD8)
/ZERO_DET_cont: TP8.1, U3.34 (PB14), U5.4
GND1: C1.1, C2.1, C5.1, C8.1, R6.1, R7.1, RS1.2, RS1.9, U1.9 (GND2), U1.15 (GND2), U2.5 (GND)
GNDA: C11.2, C12.2, C13.1, C14.2, RS2.1, RS2.4, RS2.5, RS2.6, RS2.7, RS2.10, U4.1 (IN-)
GNDD: C2.2, C3.2, C4.2, C6.2, C7.2, C9.1, C10.2, C13.2, C15.2, C16.2, C17.2, C20.2, C23.2, C26.2, J1.6, OC1.3, Q1.2 (E), Q2.2 (E), Q4.2 (E), Q6.2 (E), Q8.2 (E), Q10.2 (E), U1.2 (GND1), U1.8 (GND1), U3.9 (VSS), U4.3 (OUT-), U5.3 (GND)
unnamed: C18.1, R14.1
unnamed: C19.1, R12.1, R13.2
unnamed: C21.1, R18.1
unnamed: C22.1, R16.1, R17.2
unnamed: C24.1, R22.1
unnamed: C25.1, R20.1, R21.2
unnamed: C27.1, R26.1
unnamed: C28.1, R24.1, R25.2
unnamed: D1.2 (A), R4.1
unnamed: D1.1 (K), Q1.3 (C)
unnamed: D2.2 (A), R8.2
unnamed: D2.1 (K), Q2.3 (C)
unnamed: F4.1, F5.1, J6.1, J6.2, TP3.1
unnamed: F2.1, F3.1, J6.3, J6.4, TP2.1
unnamed: OC1.1, R10.1
unnamed: OC1.2, R9.2
unnamed: OC1.4, R11.1, TP7.1, U5.2
unnamed: OC2.1, R15.2
unnamed: OC2.6, R12.2
unnamed: OC3.1, R19.2
unnamed: OC3.6, R16.2
unnamed: OC4.1, R23.2
unnamed: OC4.6, R20.2
unnamed: OC5.1, R27.2
unnamed: OC5.6, R24.2
unnamed: Q1.1 (B), U3.21 (PA4)
unnamed: Q2.1 (B), U3.22 (PA5)
unnamed: OC2.4, Q3.3 (G)
unnamed: OC2.2, Q4.3 (C), TP11.1
unnamed: OC3.4, Q5.3 (G)
unnamed: OC3.2, Q6.3 (C), TP13.1
unnamed: OC4.4, Q7.3 (G)
unnamed: OC4.2, Q8.3 (C), TP15.1
unnamed: OC5.4, Q9.3 (G)
unnamed: OC5.2, Q10.3 (C), TP17.1
unnamed: R3.1, RS1.3, RS1.8, TP19.1, U2.6 (A)
unnamed: R6.2, RS1.4, RS1.7, TP20.1, U2.7 (B)
unnamed: F1.1, RS2.2, RS2.3, RS2.8, RS2.9
unnamed: R5.2, U1.7 (VE1)
unnamed: R1.1, U1.10 (VE2)
unnamed: R2.1, TP22.1, U1.11 (VID), U2.1 (RO)
unnamed: TP23.1, U1.13 (VOB), U2.4 (DI)
unnamed: R7.2, TP21.1, U1.12 (VOC), U2.2 (~RE), U2.3 (DE)
unnamed: C12.1, L1.2, U4.2 (IN+)
